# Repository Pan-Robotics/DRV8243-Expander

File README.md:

# DRV8243-Expander
Breakout PCB for The DRV8243 DC Motor Driver

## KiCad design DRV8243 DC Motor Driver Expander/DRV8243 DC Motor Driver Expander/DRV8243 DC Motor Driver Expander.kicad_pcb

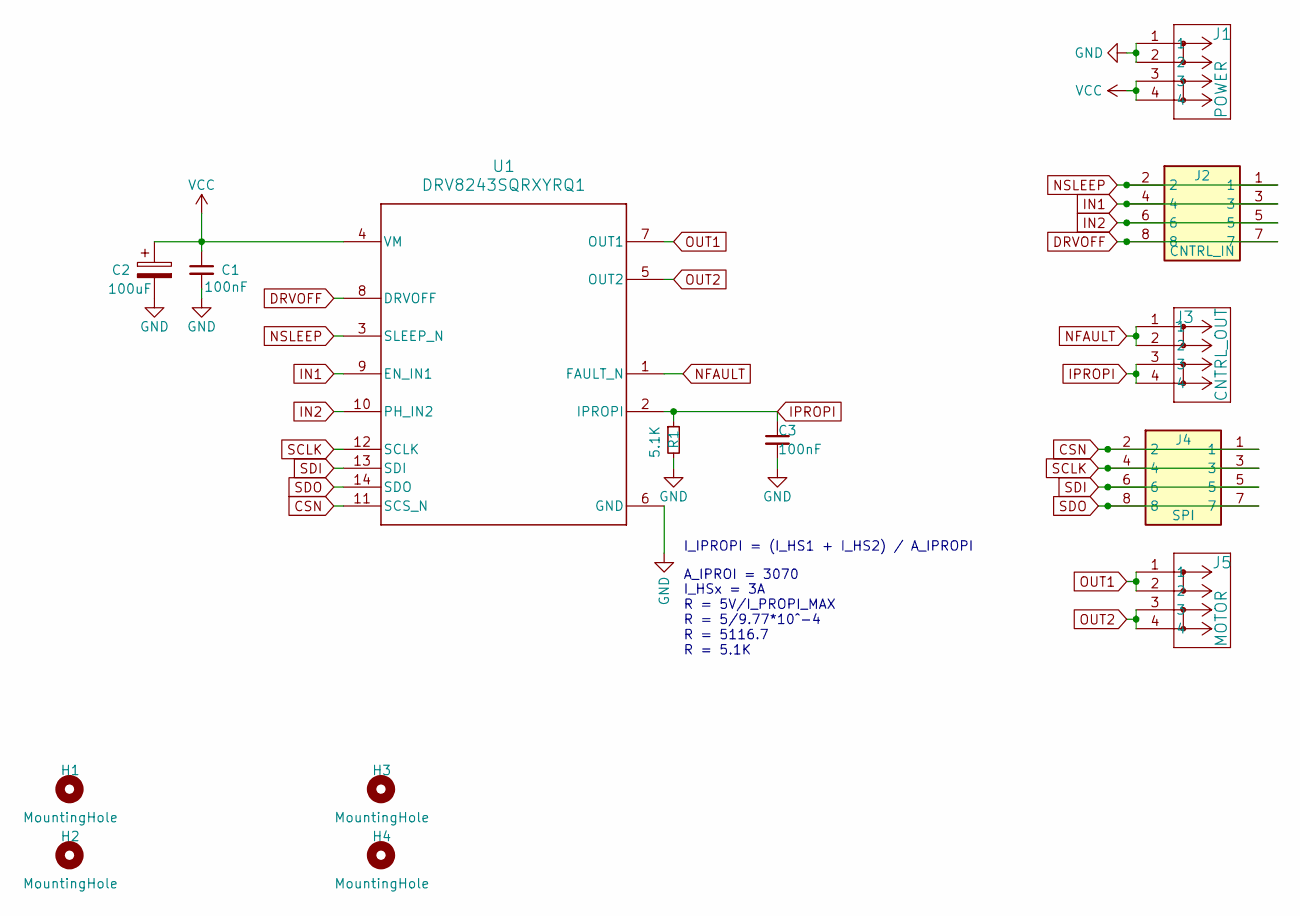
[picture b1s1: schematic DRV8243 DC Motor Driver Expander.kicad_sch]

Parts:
C1, C3: 100nF; C_1206_3216Metric_Pad1.33x1.80mm_HandSolder
C2: 100uF; C_Elec_8x10.2
H1, H2, H3, H4: MountingHole; MountingHole_3.2mm_M3_Pad_Via
J1: POWER; CONN_1862042
J2: CNTRL_IN; 1862068; Mouser Part Number 651-1862068
J3: CNTRL_OUT; CONN_1862042
J4: SPI; 1862068; Mouser Part Number 651-1862068
J5: MOTOR; CONN_1862042
R1: 5.1K; R_1206_3216Metric_Pad1.30x1.75mm_HandSolder
U1: DRV8243SQRXYRQ1; RXY0014A-MFG

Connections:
CSN: J4.1, J4.2, U1.11 (SCS_N)
DRVOFF: J2.7, J2.8, U1.8 (DRVOFF)
GND: C1.2, C2.2, C3.2, J1.1, J1.2, R1.2, U1.6 (GND), U1.20, U1.21
IN1: J2.3, J2.4, U1.9 (EN_IN1)
IN2: J2.5, J2.6, U1.10 (PH_IN2)
IPROPI: C3.1, J3.3, J3.4, R1.1, U1.2 (IPROPI)
NFAULT: J3.1, J3.2, U1.1 (FAULT_N)
NSLEEP: J2.1, J2.2, U1.3 (SLEEP_N)
OUT1: J5.1, J5.2, U1.7 (OUT1), U1.19
OUT2: J5.3, J5.4, U1.5 (OUT2), U1.18
SCLK: J4.3, J4.4, U1.12 (SCLK)
SDI: J4.5, J4.6, U1.13 (SDI)
SDO: J4.7, J4.8, U1.14 (SDO)
VCC: C1.1, C2.1, J1.3, J1.4, U1.4 (VM), U1.15, U1.16, U1.17

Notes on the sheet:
I_HSx = 3A R = 5V/I_PROPI_MAX R = 5/9.77*10^-4 R = 5116.7 R = 5.1K
A_IPROI = 3070
I_IPROPI = (I_HS1 + I_HS2) / A_IPROPI

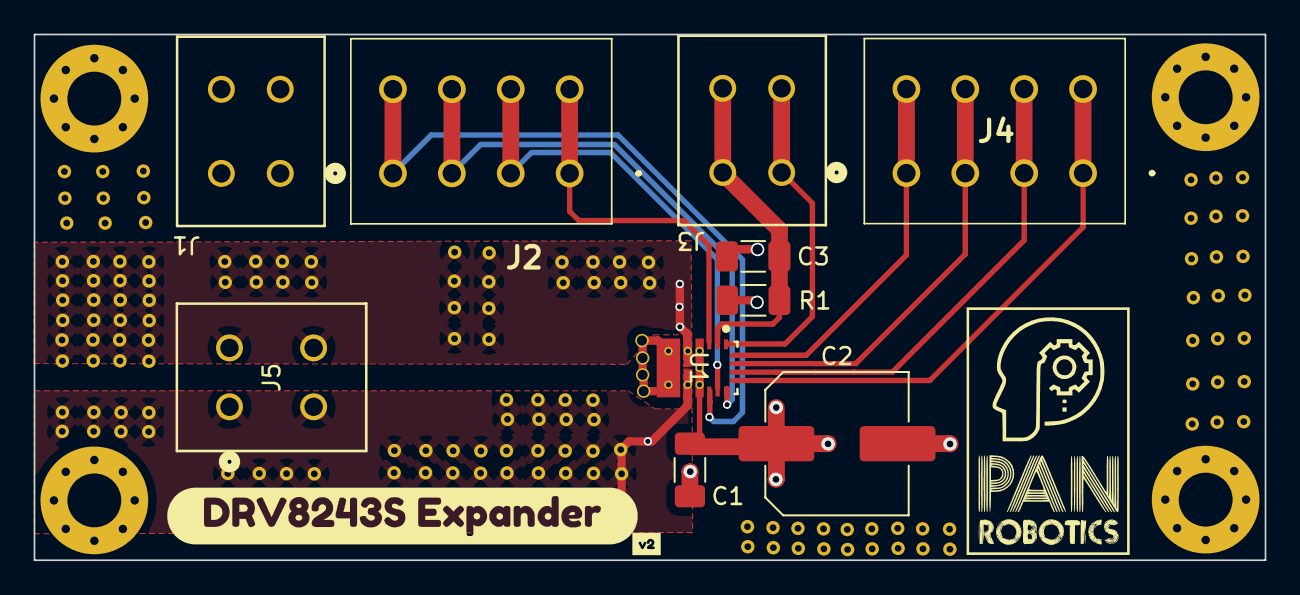
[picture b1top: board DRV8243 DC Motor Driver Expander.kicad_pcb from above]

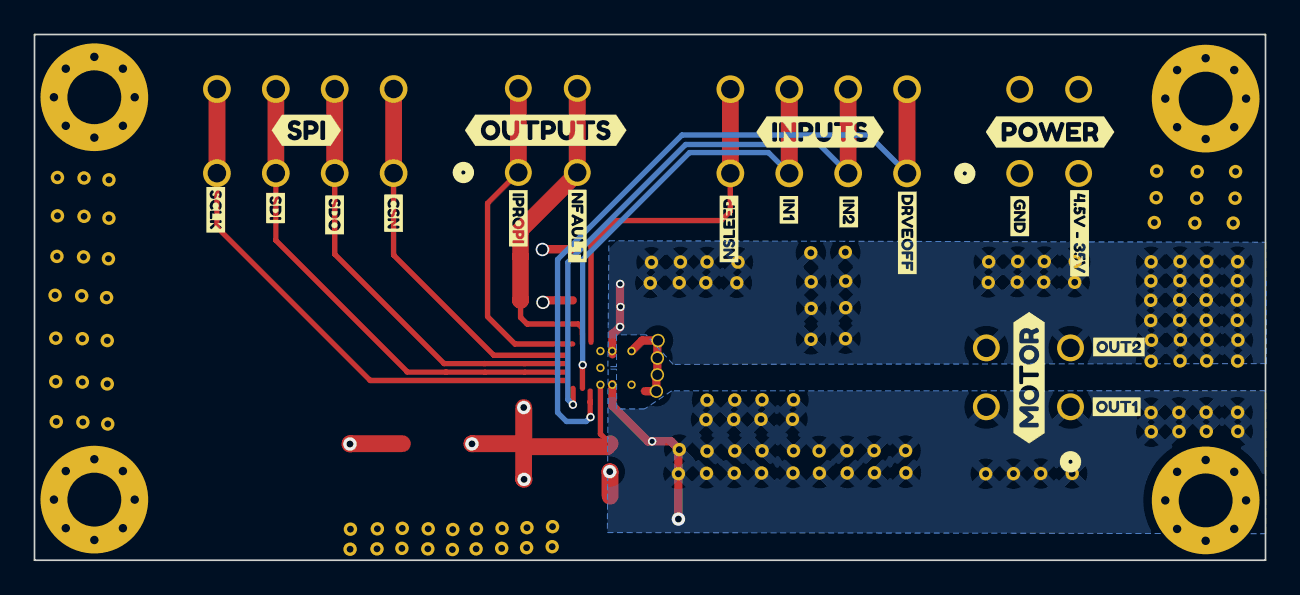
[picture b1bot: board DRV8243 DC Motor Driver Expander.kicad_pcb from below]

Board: 4 copper layers, 73.2 x 31.2 mm, 35 parts (19 on the bottom side), 14 nets.

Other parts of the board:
kibuzzard-65A6FC0C: G***; kibuzzard-65A6FC0C
kibuzzard-65A6FCAC: G***; kibuzzard-65A6FCAC
kibuzzard-65A6FCCE: G***; kibuzzard-65A6FCCE
kibuzzard-65A6FCD9: G***; kibuzzard-65A6FCD9
kibuzzard-65A6FCE2: G***; kibuzzard-65A6FCE2
kibuzzard-65A6FD3E: G***; kibuzzard-65A6FD3E
kibuzzard-65A6FD04: G***; kibuzzard-65A6FD04
kibuzzard-65A6FD36: G***; kibuzzard-65A6FD36
kibuzzard-65A6FFF9: G***; kibuzzard-65A6FFF9
kibuzzard-65A7000E: G***; kibuzzard-65A7000E
kibuzzard-65A7001B: G***; kibuzzard-65A7001B
kibuzzard-65A70003: G***; kibuzzard-65A70003
kibuzzard-65BE5B0F: G***; kibuzzard-65BE5B0F
kibuzzard-65BE5B8E: G***; kibuzzard-65BE5B8E
kibuzzard-65BE5B66: G***; kibuzzard-65BE5B66
kibuzzard-65BE5BEC: G***; kibuzzard-65BE5BEC
kibuzzard-65BE5BF3: G***; kibuzzard-65BE5BF3
kibuzzard-65BE5BFB: G***; kibuzzard-65BE5BFB
kibuzzard-65BE5C01: G***; kibuzzard-65BE5C01
kibuzzard-65BE5C3B: G***; kibuzzard-65BE5C3B
kibuzzard-66B25C50: G***; kibuzzard-66B25C50

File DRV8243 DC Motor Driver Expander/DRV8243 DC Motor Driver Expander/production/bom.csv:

Designator,Footprint,Quantity,Value,LCSC Part #
"_138, _137, _136, _135, _134, _133, _132, _131, _130, _129, _128, _127, _126, _125, _124, _123, _122, _121, _120, _119, _118, _117, _116, _115, _114, _113, _112, _111, _110, _109, _108, _107, _106, _105, _104, _103, _102, _101, _100, _99, _98, _97, _96, _95, _94, _93, _92, _91, _90, _89, _88, _87, _86, _85, _84, _83, _82, _81, _80, _79, _78, _77, _76, _75, _74, _73, _72, _71, _70, _69, _68, _67, _66, _65, _64, _63, _62, _61, _60, _59, _58, _57, _56, _55, _54, _53, _52, _51, _50, _49, _48, _47, _46, _45, _44, _43, _42, _41, _40, _39, _38, _37, _36, _35, _34, _33, _32, _31, _30, _29, _28, _27, _26, _25, _24, _23, _22, _21, _20, _19, _18, _17, _16, _15, _14, _13, _12, _11, _10, _9, _8, _7, _6, _5, _4, _3, _2, ",,138,,
"C1, C3",1206,2,100nF,
C2,C_Elec_8x10.2,1,100uF,
"H1, H2, H3, H4",MountingHole_3.2mm_M3_Pad_Via,4,MountingHole,
J1,CONN_1862042,1,POWER,
J2,1862068,1,CNTRL_IN,
J3,CONN_1862042,1,CNTRL_OUT,
J4,1862068,1,SPI,
J5,CONN_1862042,1,MOTOR,
R1,1206,1,5.1K,
U1,RXY0014A-MFG,1,DRV8243SQRXYRQ1,

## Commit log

2024-02-03 DRV8243 Driver Expander Created
2024-03-01 PCB Photos Added
2024-08-06 V2 Board
